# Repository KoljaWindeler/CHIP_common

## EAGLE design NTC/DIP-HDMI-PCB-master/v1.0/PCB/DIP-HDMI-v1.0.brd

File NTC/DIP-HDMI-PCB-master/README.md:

# Source Files
C.H.I.P. HDMI Display DIP is designed using Eagle!

# DIP-HDMI-PCB

HDMI DIP = v1.0

#License
<br />This work is licensed under a <a rel="license" href="http://creativecommons.org/licenses/by-sa/3.0/us/">Creative Commons Attribution-ShareAlike 3.0 United States License</a>.

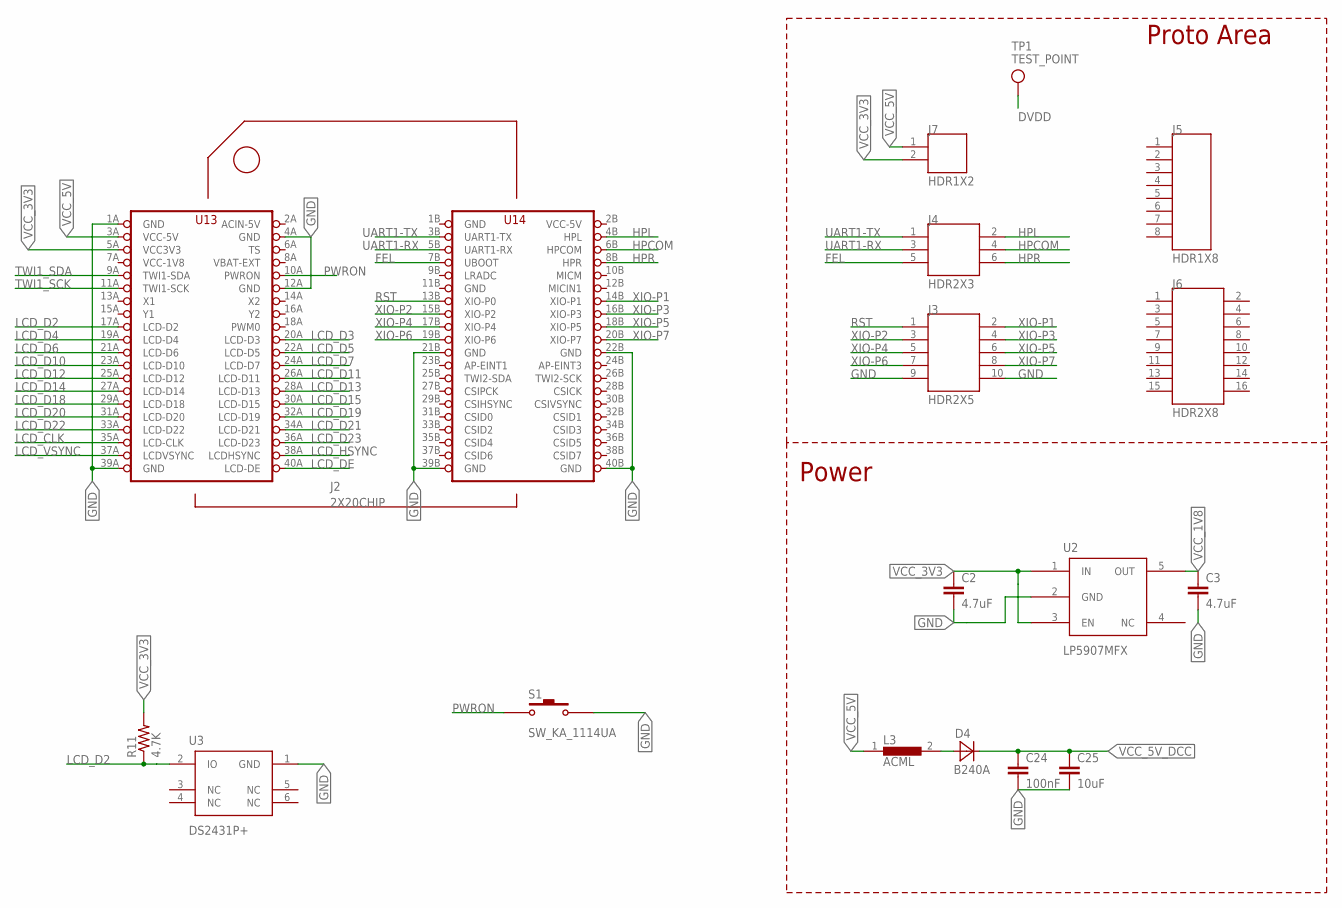
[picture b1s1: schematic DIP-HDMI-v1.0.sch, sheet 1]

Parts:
C2, C3: 4.7uF; 1608_0603
C24: 100nF; 1608_0603
C25: 10uF; 1608_0603
D4: B240A; SMA
J2: 2X20CHIP; HDR2X2X20H
J3: HDR2X5
J4: HDR2X3
J5: HDR1X8
J6: HDR2X8
J7: HDR1X2
L3: ACML; 0603
R11: 4.7K; J1-0603
S1: SW_KA_1114UA
TP1: TEST_POINT; TP-1MMX1MM
U2: LP5907MFX; SOT23-5
U3: DS2431P+; DS2431P+T&R

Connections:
DVDD: TP1.0; also elsewhere on the board
FEL: J2.7B (UBOOT), J4.5
GND: C2.2, C3.2, C24.2, C25.2, J2.1A (GND), J2.1B (GND), J2.4A (GND), J2.11B (GND), J2.12A (GND), J2.21B (GND), J2.22B (GND), J2.39A (GND), J2.39B (GND), J2.40B (GND), J3.9, J3.10, S1.3 (2), S1.4 (2), U2.2 (GND), U3.1 (GND); also elsewhere on the board
HPCOM: J2.6B (HPCOM), J4.4
HPL: J2.4B (HPL), J4.2
HPR: J2.8B (HPR), J4.6
LCD_CLK: J2.35A (LCD-CLK); also elsewhere on the board
LCD_D2: J2.17A (LCD-D2), R11.1, U3.2 (IO)
LCD_D3: J2.20A (LCD-D3); also elsewhere on the board
LCD_D4: J2.19A (LCD-D4); also elsewhere on the board
LCD_D5: J2.22A (LCD-D5); also elsewhere on the board
LCD_D6: J2.21A (LCD-D6); also elsewhere on the board
LCD_D7: J2.24A (LCD-D7); also elsewhere on the board
LCD_D10: J2.23A (LCD-D10); also elsewhere on the board
LCD_D11: J2.26A (LCD-D11); also elsewhere on the board
LCD_D12: J2.25A (LCD-D12); also elsewhere on the board
LCD_D13: J2.28A (LCD-D13); also elsewhere on the board
LCD_D14: J2.27A (LCD-D14); also elsewhere on the board
LCD_D15: J2.30A (LCD-D15); also elsewhere on the board
LCD_D18: J2.29A (LCD-D18); also elsewhere on the board
LCD_D19: J2.32A (LCD-D19); also elsewhere on the board
LCD_D20: J2.31A (LCD-D20); also elsewhere on the board
LCD_D21: J2.34A (LCD-D21); also elsewhere on the board
LCD_D22: J2.33A (LCD-D22); also elsewhere on the board
LCD_D23: J2.36A (LCD-D23); also elsewhere on the board
LCD_DE: J2.40A (LCD-DE); also elsewhere on the board
LCD_HSYNC: J2.38A (LCDHSYNC); also elsewhere on the board
LCD_VSYNC: J2.37A (LCDVSYNC); also elsewhere on the board
unnamed: D4.1 (A), L3.2
PWRON: J2.10A (PWRON), S1.1, S1.2 (1)
RST: J2.13B (XIO-P0), J3.1; also elsewhere on the board
TWI1_SCK: J2.11A (TWI1-SCK); also elsewhere on the board
TWI1_SDA: J2.9A (TWI1-SDA); also elsewhere on the board
UART1-RX: J2.5B (UART1-RX), J4.3
UART1-TX: J2.3B (UART1-TX), J4.1
VCC-1V8: J2.7A (VCC-1V8)
VCC-5V: J2.2B (VCC-5V)
VCC_1V8: C3.1, U2.5 (OUT); also elsewhere on the board
VCC_3V3: C2.1, J2.5A (VCC3V3), J7.2, R11.2, U2.1 (IN), U2.3 (EN); also elsewhere on the board
VCC_5V: J2.3A (VCC-5V), J7.1, L3.1
VCC_5V_DCC: C24.1, C25.1, D4.2 (C); also elsewhere on the board
XIO-P1: J2.14B (XIO-P1), J3.2
XIO-P2: J2.15B (XIO-P2), J3.3
XIO-P3: J2.16B (XIO-P3), J3.4
XIO-P4: J2.17B (XIO-P4), J3.5
XIO-P5: J2.18B (XIO-P5), J3.6
XIO-P6: J2.19B (XIO-P6), J3.7
XIO-P7: J2.20B (XIO-P7), J3.8

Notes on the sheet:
Proto Area
Power

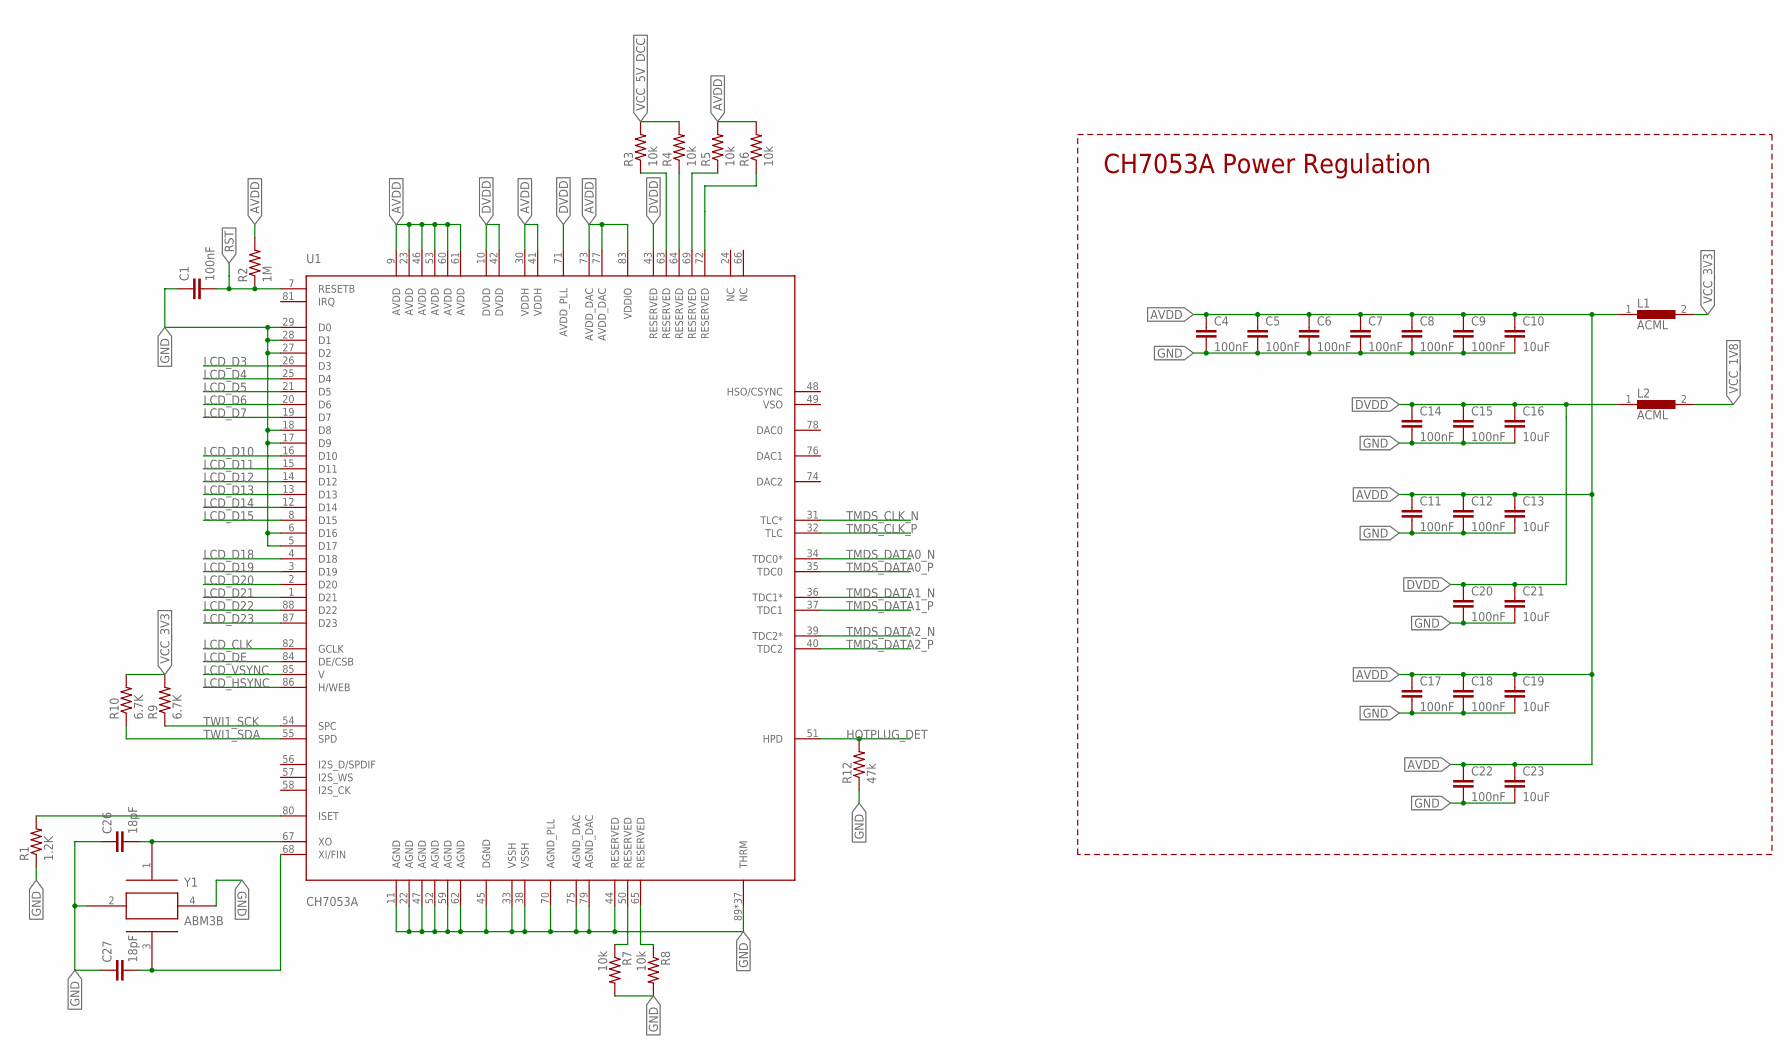
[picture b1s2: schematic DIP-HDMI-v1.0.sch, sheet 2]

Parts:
C1, C4, C5, C6, C7, C8, C9, C11, C12, C14, C15, C17, C18, C20, C22: 100nF; 1608_0603
C10, C13, C16, C19, C21, C23: 10uF; 1608_0603
C26, C27: 18pF; 1608_0603
L1, L2: ACML; 0603
R1: 1.2K; J1-0603
R2: 1M; J1-0603
R3, R4, R5, R6, R7, R8: 10k; J1-0603
R9, R10: 6.7K; J1-0603
R12: 47k; J1-0603
U1: CH7053A; QFN40P1000X1000X90_HS-89M
Y1: ABM3B

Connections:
AVDD: C4.1, C5.1, C6.1, C7.1, C8.1, C9.1, C10.1, C11.1, C12.1, C13.1, C17.1, C18.1, C19.1, C22.1, C23.1, L1.1, R2.2, R5.2, R6.2, U1.9 (AVDD), U1.23 (AVDD), U1.30 (VDDH), U1.41 (VDDH), U1.46 (AVDD), U1.53 (AVDD), U1.60 (AVDD), U1.61 (AVDD), U1.73 (AVDD_DAC), U1.77 (AVDD_DAC), U1.83 (VDDIO)
DVDD: C14.1, C15.1, C16.1, C20.1, C21.1, L2.1, U1.10 (DVDD), U1.42 (DVDD), U1.43 (RESERVED), U1.71 (AVDD_PLL); also elsewhere on the board
GND: C1.1, C4.2, C5.2, C6.2, C7.2, C8.2, C9.2, C10.2, C11.2, C12.2, C13.2, C14.2, C15.2, C16.2, C17.2, C18.2, C19.2, C20.2, C21.2, C22.2, C23.2, C26.1, C27.1, R1.1, R7.2, R8.2, R12.1, U1.5 (D17), U1.6 (D16), U1.11 (AGND), U1.17 (D9), U1.18 (D8), U1.22 (AGND), U1.27 (D2), U1.28 (D1), U1.29 (D0), U1.33 (VSSH), U1.38 (VSSH), U1.44 (RESERVED), U1.45 (DGND), U1.47 (AGND), U1.52 (AGND), U1.59 (AGND), U1.62 (AGND), U1.70 (AGND_PLL), U1.75 (AGND_DAC), U1.79 (AGND_DAC), U1.89 (THRM), U1.P$1 (THRM), U1.P$2 (THRM), U1.P$3 (THRM), U1.P$4 (THRM), U1.P$5 (THRM), U1.P$6 (THRM), U1.P$7 (THRM), U1.P$8 (THRM), U1.P$9 (THRM), U1.P$10 (THRM), U1.P$11 (THRM), U1.P$12 (THRM), U1.P$13 (THRM), U1.P$14 (THRM), U1.P$15 (THRM), U1.P$16 (THRM), U1.P$17 (THRM), U1.P$18 (THRM), U1.P$19 (THRM), U1.P$20 (THRM), U1.P$21 (THRM), U1.P$22 (THRM), U1.P$23 (THRM), U1.P$24 (THRM), U1.P$25 (THRM), U1.P$26 (THRM), U1.P$27 (THRM), U1.P$28 (THRM), U1.P$29 (THRM), U1.P$30 (THRM), U1.P$31 (THRM), U1.P$32 (THRM), U1.P$33 (THRM), U1.P$34 (THRM), U1.P$35 (THRM), U1.P$36 (THRM), Y1.2, Y1.4; also elsewhere on the board
HOTPLUG_DET: R12.2, U1.51 (HPD); also elsewhere on the board
LCD_CLK: U1.82 (GCLK); also elsewhere on the board
LCD_D3: U1.26 (D3); also elsewhere on the board
LCD_D4: U1.25 (D4); also elsewhere on the board
LCD_D5: U1.21 (D5); also elsewhere on the board
LCD_D6: U1.20 (D6); also elsewhere on the board
LCD_D7: U1.19 (D7); also elsewhere on the board
LCD_D10: U1.16 (D10); also elsewhere on the board
LCD_D11: U1.15 (D11); also elsewhere on the board
LCD_D12: U1.14 (D12); also elsewhere on the board
LCD_D13: U1.13 (D13); also elsewhere on the board
LCD_D14: U1.12 (D14); also elsewhere on the board
LCD_D15: U1.8 (D15); also elsewhere on the board
LCD_D18: U1.4 (D18); also elsewhere on the board
LCD_D19: U1.3 (D19); also elsewhere on the board
LCD_D20: U1.2 (D20); also elsewhere on the board
LCD_D21: U1.1 (D21); also elsewhere on the board
LCD_D22: U1.88 (D22); also elsewhere on the board
LCD_D23: U1.87 (D23); also elsewhere on the board
LCD_DE: U1.84 (DE/CSB); also elsewhere on the board
LCD_HSYNC: U1.86 (H/WEB); also elsewhere on the board
LCD_VSYNC: U1.85 (V); also elsewhere on the board
unnamed: C26.2, U1.67 (XO), Y1.1
unnamed: C27.2, U1.68 (XI/FIN), Y1.3
unnamed: R1.2, U1.80 (ISET)
unnamed: R7.1, U1.50 (RESERVED)
unnamed: R8.1, U1.65 (RESERVED)
unnamed: R5.1, U1.69 (RESERVED)
unnamed: R3.1, U1.63 (RESERVED)
unnamed: R4.1, U1.64 (RESERVED)
unnamed: R6.1, U1.72 (RESERVED)
RST: C1.2, R2.1, U1.7 (RESETB); also elsewhere on the board
TMDS_CLK_N: U1.31 (TLC*); also elsewhere on the board
TMDS_CLK_P: U1.32 (TLC); also elsewhere on the board
TMDS_DATA0_N: U1.34 (TDC0*); also elsewhere on the board
TMDS_DATA0_P: U1.35 (TDC0); also elsewhere on the board
TMDS_DATA1_N: U1.36 (TDC1*); also elsewhere on the board
TMDS_DATA1_P: U1.37 (TDC1); also elsewhere on the board
TMDS_DATA2_N: U1.39 (TDC2*); also elsewhere on the board
TMDS_DATA2_P: U1.40 (TDC2); also elsewhere on the board
TWI1_SCK: R9.1, U1.54 (SPC); also elsewhere on the board
TWI1_SDA: R10.1, U1.55 (SPD); also elsewhere on the board
VCC_1V8: L2.2; also elsewhere on the board
VCC_3V3: L1.2, R9.2, R10.2; also elsewhere on the board
VCC_5V_DCC: R3.2, R4.2; also elsewhere on the board

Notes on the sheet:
CH7053A Power Regulation

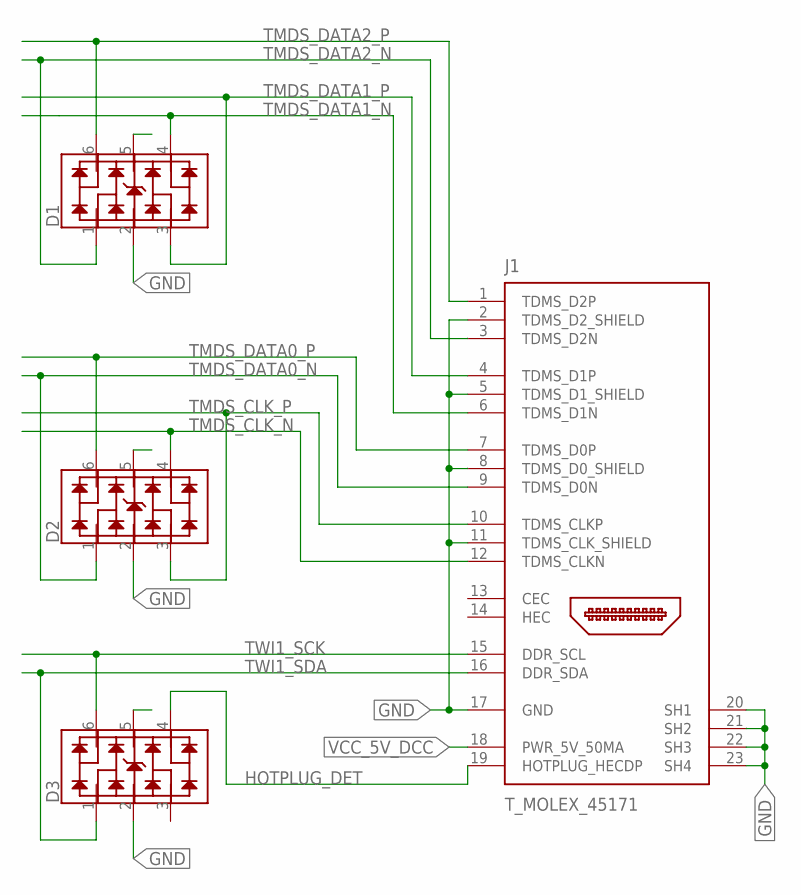
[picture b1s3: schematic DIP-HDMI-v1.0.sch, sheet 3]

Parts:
D1, D2, D3: D-SEMTECH-RCLAMP0504S; T_SOT95P285X90-6N
J1: T_MOLEX_45171

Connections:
GND: D1.2, D2.2, D3.2, J1.2 (TDMS_D2_SHIELD), J1.5 (TDMS_D1_SHIELD), J1.8 (TDMS_D0_SHIELD), J1.11 (TDMS_CLK_SHIELD), J1.17 (GND), J1.20 (SH1), J1.21 (SH2), J1.22 (SH3), J1.23 (SH4); also elsewhere on the board
HOTPLUG_DET: D3.4, J1.19 (HOTPLUG_HECDP); also elsewhere on the board
TMDS_CLK_N: D2.4, J1.12 (TDMS_CLKN); also elsewhere on the board
TMDS_CLK_P: D2.3, J1.10 (TDMS_CLKP); also elsewhere on the board
TMDS_DATA0_N: D2.1, J1.9 (TDMS_D0N); also elsewhere on the board
TMDS_DATA0_P: D2.6, J1.7 (TDMS_D0P); also elsewhere on the board
TMDS_DATA1_N: D1.4, J1.6 (TDMS_D1N); also elsewhere on the board
TMDS_DATA1_P: D1.3, J1.4 (TDMS_D1P); also elsewhere on the board
TMDS_DATA2_N: D1.1, J1.3 (TDMS_D2N); also elsewhere on the board
TMDS_DATA2_P: D1.6, J1.1 (TDMS_D2P); also elsewhere on the board
TWI1_SCK: D3.6, J1.15 (DDR_SCL); also elsewhere on the board
TWI1_SDA: D3.1, J1.16 (DDR_SDA); also elsewhere on the board
VCC_5V_DCC: J1.18 (PWR_5V_50MA); also elsewhere on the board

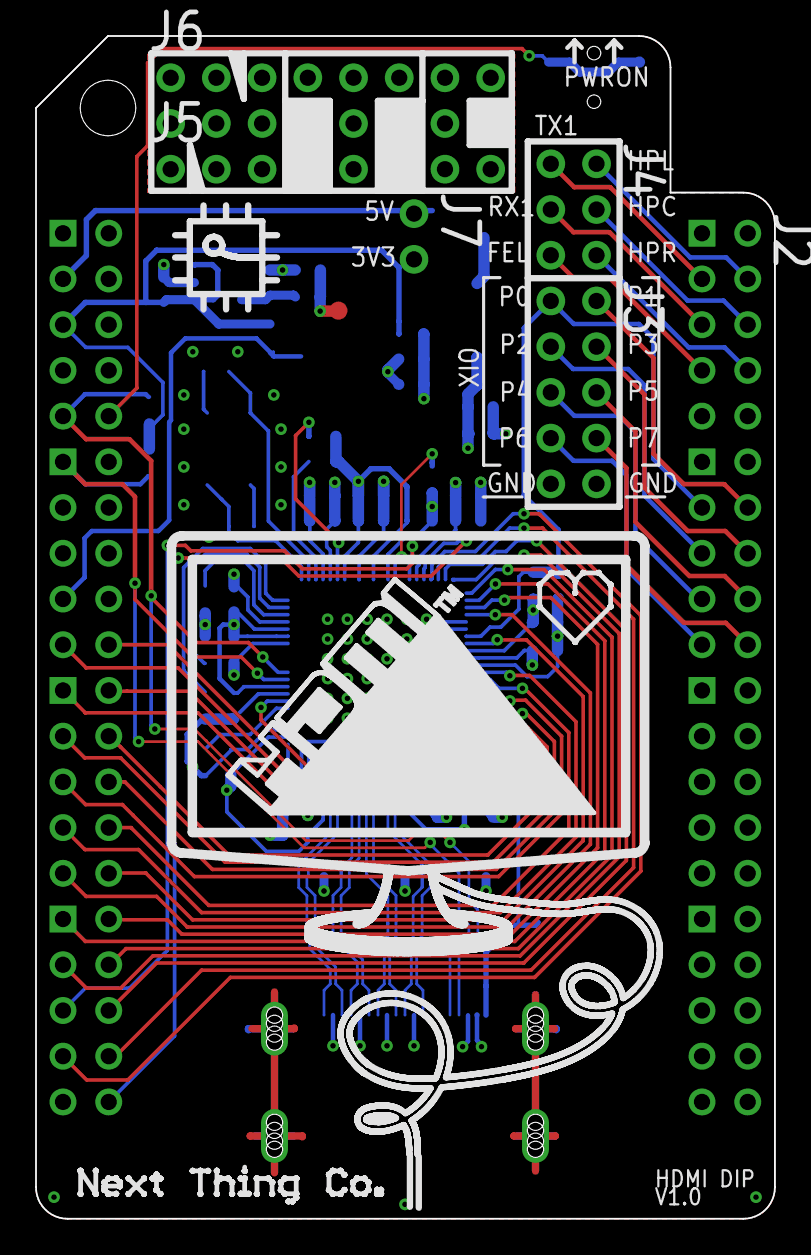
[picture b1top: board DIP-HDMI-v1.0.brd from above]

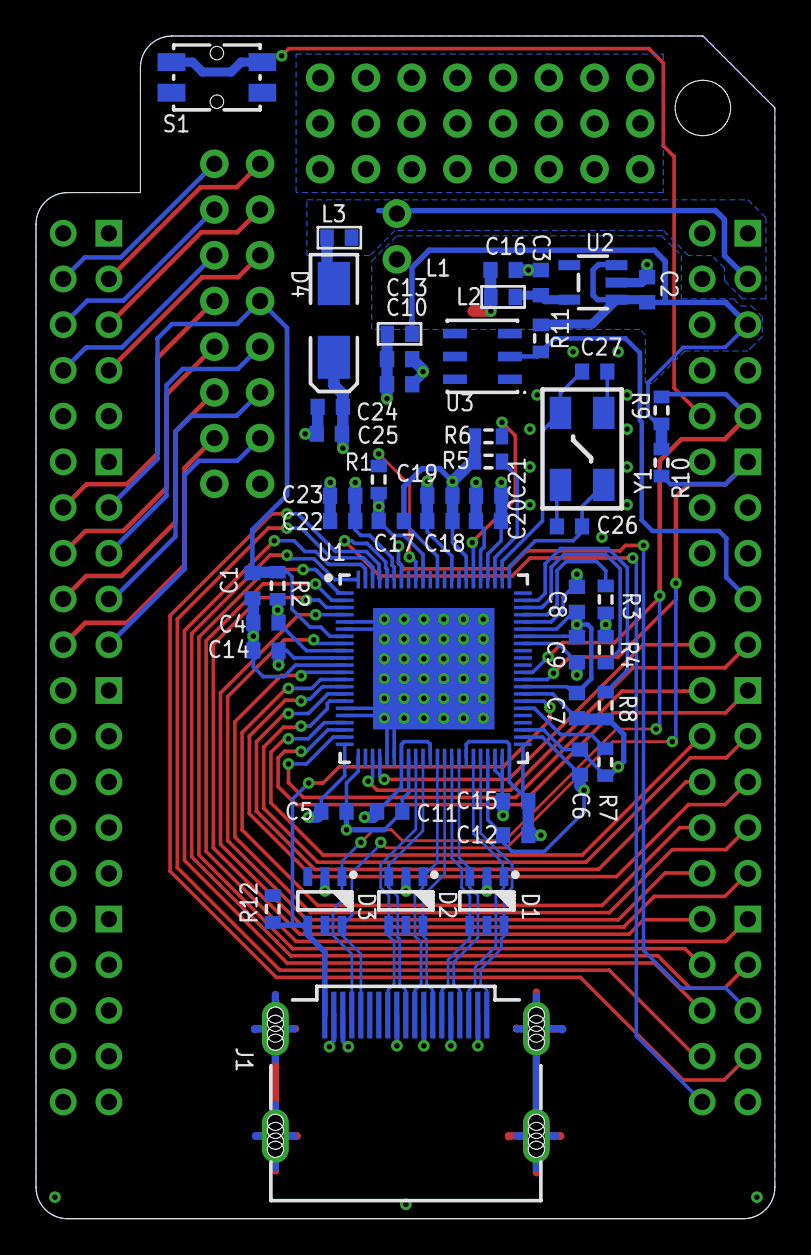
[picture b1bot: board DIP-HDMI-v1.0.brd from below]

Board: 4 copper layers, 41.0 x 65.7 mm, 60 parts (52 on the bottom side), 65 nets.

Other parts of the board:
U$2: MOUNTINGHOLE

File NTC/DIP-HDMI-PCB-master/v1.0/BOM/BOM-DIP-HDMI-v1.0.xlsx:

| Company = Next Thing Co
 | Design Title =HDMI Adapter
 | Doc Name: BOM-DIP-HDMI-v1.0.xlsx
 | Matching PCB: DIP-HDMI-v1.0.brd
 | Schematics REV: 1.0
 | Qty | Parts | VALUE | Item number | TOLERANCE | DESCRIPTION | FOOTPRINT | MFG | MFG_PN | PART_TYPE
 | 16 | C1, C4, C5, C6, C7, C8, C9, C11, C12, C14, C15, C17, C18, C20, C22, C24 | 100nF | 100364 | 0.1 | CAP CER SMD 100nF 16V X5R 10% 0603 | 0603 | SAMSUNG | CL10B104KO8NNNL | CAP
 | 2 | C2, C3 | 4.7uF | 100365 | 0.1 | CAP CER SMD 4.7uF 10V X5R 10% 0603 | 0603 | SAMSUNG | CL10A475KP8NNNL | CAP
 | 7 | C10, C13, C16, C19, C21, C23, C25 | 10uF | 100366 | 0.1 | CAP CER SMD 10uF 10V X5R 10% 0603 | 0603 | SAMSUNG | CL10A106KP8NNND | CAP
 | 2 | C26, C27 | 18pF | 100367 | 0.01 | CAP CER SMD 18pF 50V NP0 1% 0603 | 0603 | SAMSUNG | CL10C180JB8NNND | CAP
 | 1 | J1 | HDMI Con | 100402 |  | Connector Receptacle HDMI 19 Position Surface Mount, Right Angle, Horizontal |  | Zhixingda | 71-050-190111-1 | CON
 | 2 | J2A, J2B | CON2X20 | 100401 |  | 2x Con male through hole 40 pos, 2 rows, 2.54MM | 2XHDR_40POS_PTH_254MM | TE Connectivity | 2 x 1-102567-2 | CON
 | 1 | R1 | 1.2k | 100368 | 0.01 | RES SMD 1.2K Ohm 1/16W 1% 0603 | 0603 | YAGEO | RC0603FR-071K2L | RES
 | 1 | R2 | 1M | 100369 | 0.05 | RES SMD 1M Ohm 1/16W 5% 0603 | 0603 | YAGEO | RC0603JR-071ML | RES
 | 6 | R3, R4, R5, R6, R7, R8 | 10k | 100370 | 0.05 | RES SMD 10K Ohm 1/16W 5% 0603 | 0603 | YAGEO | RC0603JR-0710KL | RES
 | 2 | R9, R10 | 6.8k | 100406 | 0.05 | RES SMD 6.8K Ohm 1/16W 5% 0603 | 0603 | YAGEO | RC0603JR-076K8L | RES
 | 1 | R11 | 4.7k | 100380 | 0.05 | RES SMD 4.7K Ohm 1/16W 5% 0603 | 0603 | YAGEO | RC0603JR-074K7L | RES
 | 1 | R12 | 47k | 100381 | 0.05 | RES SMD 47K Ohm 1/16W 5% 0603 | 0603 | YAGEO | RC0603JR-0747KL | RES
 | 1 | D4 | B240A | 100198 |  | DIODE SMD General Purpose 400V 1A 1.4W RoHS DO-214AC | SMA | DIODES INC | B240A-13-F | DIODE
 | 3 | D1, D2, D3 | SESRV05-4 | 100415 |  | LOW CAP TVS ARRAY | SOT-23 6 | SEMIWILL | SESRV05-4 | TVS DIODE
 | 3 | L1, L2, L3 | ACML0603 | 100417 |  | SMD Ferrite 0603, 31 Ohm @ 100MHz | 0603 | Abracon | ACML-0603-310-T | FB
 | 1 | U1 | CH7035B | 100404 |  | IC, LDC to HDTV/VGA/DVI, QFN88 | QFN88 | Chrontel | CH7035B | IC
 | 1 | U2 | BL9198-18 | 100416 |  | LDO SMD, 1.8V, 250mA SOT-23 | SOT-23 5 | Shanghai Belling | BL9198-18 | IC
 | 1 | U3 | DS2431 | 100312 |  | IC, EEPROM, 1KBIT, TSOC 6 | TSOC 6 | Maxim Integrated | DS2431P+T&R | IC
 | 1 | Y1 | ABM3B | 100418 |  | CRYSTAL SMD 5X3.2 27Mhz 20ppm 18pF | 5X3.2mm | Abracon | ABM3B-27.000MHZ-B2-T | XTAL
 | 1 |  | PCB | 100422 |  | 4 Layer, Matte Black Mask, Pink Silk, HASL, 1 Oz |  |  | v1.0 | PCB
 | 1 |  |  |  |  | ESD BAG |  |  |  | PACKAGING
 | 1 |  |  |  |  | ESD Foam, Back Side |  |  |  | PACKAGING
 | 1 |  |  |  |  | ESD Foam, Front Side |  |  |  | PACKAGING
 | 1 | S1 | Switch | 100421 |  | Tact Switch Right Angle | 2.7X6.6mm | HRD | KA-1114UN | Switch

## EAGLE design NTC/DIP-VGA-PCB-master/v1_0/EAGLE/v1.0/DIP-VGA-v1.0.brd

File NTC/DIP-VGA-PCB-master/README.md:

# Source Files
VGA DIP is designed using Eagle CAD!

# DIP-VGA-PCB
VGA DIP = v1.0

#License
<br />This work is licensed under a <a rel="license" href="http://creativecommons.org/licenses/by-sa/3.0/us/">Creative Commons Attribution-ShareAlike 3.0 United States License</a>.

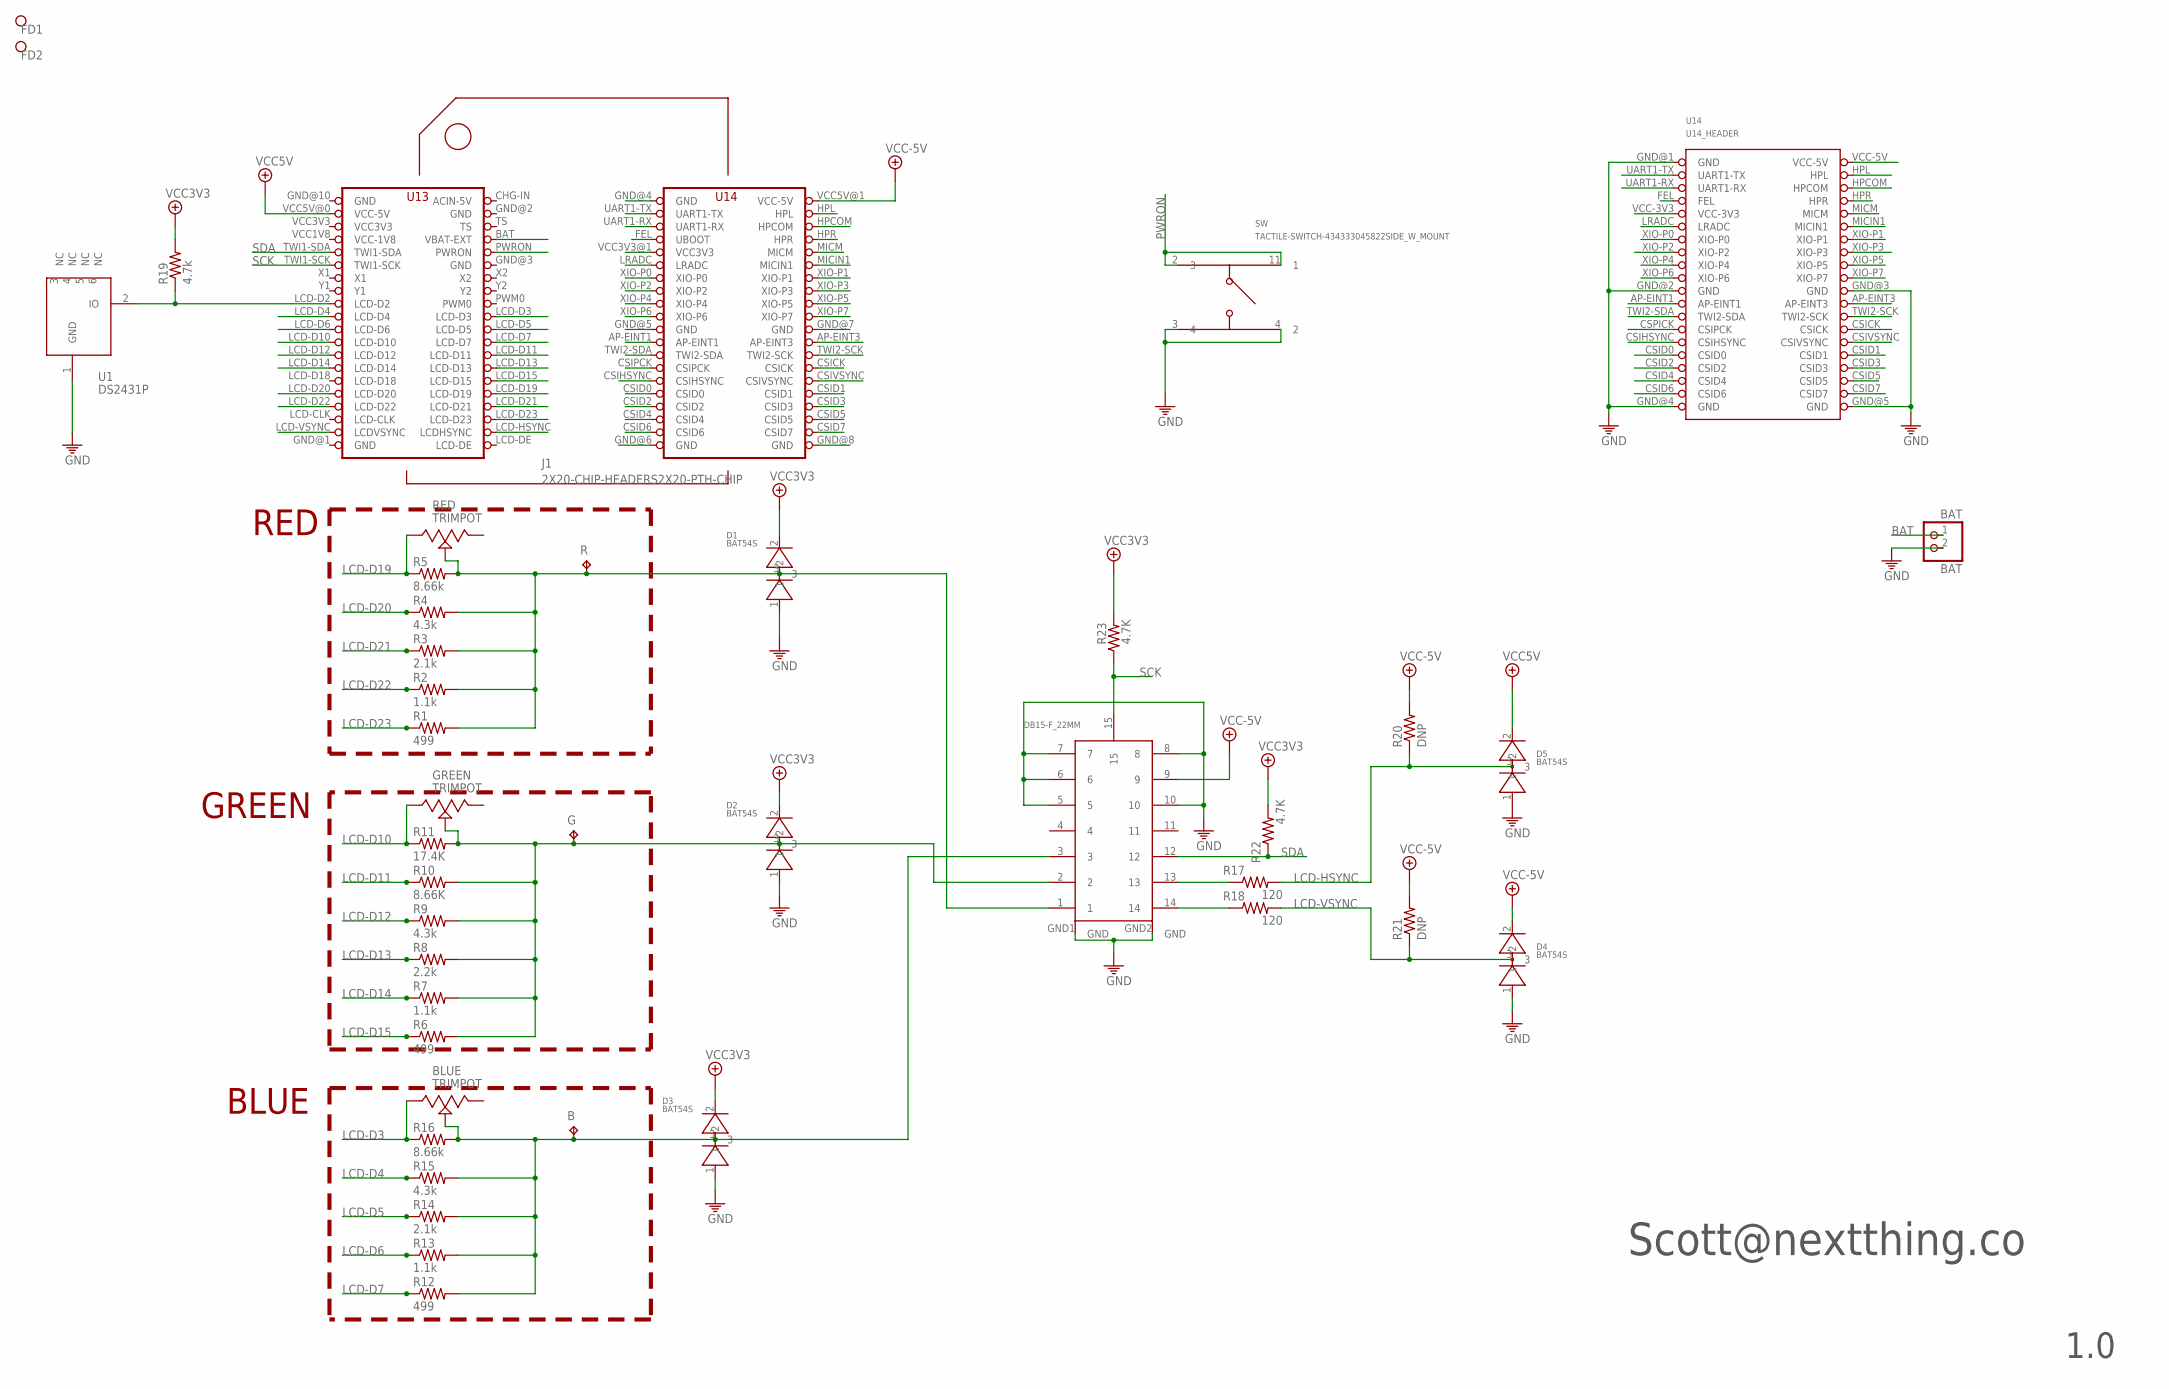
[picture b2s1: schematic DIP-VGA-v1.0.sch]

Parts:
B: TPPAD1-17; P1-17
BAT: BAT; JST-PH-2-THM-RA
BLUE: TRIMPOT
D1, D2, D3, D4, D5: BAT54S; SOT23-BEC
FD1, FD2: FIDUCIAL; FIDUCIAL_1MM
G: TPPAD1-17; P1-17
GREEN: TRIMPOT
J1: 2X20-CHIP-HEADERS2X20-PTH-CHIP; 2X20CHIP-TH
R: TPPAD1-17; P1-17
R1, R6, R12: 499; R0603_5MIL_DWS
R2, R7, R13: 1.1k; R0603_5MIL_DWS
R3, R14: 2.1k; R0603_5MIL_DWS
R4, R9, R15: 4.3k; R0603_5MIL_DWS
R5, R16: 8.66k; R0603_5MIL_DWS
R8: 2.2k; R0603_5MIL_DWS
R10: 8.66K; R0603_5MIL_DWS
R11: 17.4K; R0603_5MIL_DWS
R17, R18: 120; R0603_5MIL_DWS
R19: 4.7k; R0603_5MIL_DWS
R20, R21: DNP; R0603_5MIL_DWS
R22, R23: 4.7K; R0603_5MIL_DWS
RED: TRIMPOT
SW: TACTILE-SWITCH-434333045822SIDE_W_MOUNT; TACTILE-SWITCH-K2-1114UA-AW
TRANS(>^_^)>: DB15-F_22MM
U1: DS2431P; TSOC6
U14: U14_HEADER; U14HEADER

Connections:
1: J1.CSIVSYNC, U14.CSIVSYNC
AP-EINT1: J1.AP-EINT1, U14.AP-EINT1
AP-EINT3: J1.AP-EINT3, U14.AP-EINT3
BAT: BAT.1 (2), J1.BAT (VBAT-EXT)
CSICK: J1.CSICK, U14.CSICK
CSID0: J1.CSID0, U14.CSID0
CSID1: J1.CSID1, U14.CSID1
CSID2: J1.CSID2, U14.CSID2
CSID3: J1.CSID3, U14.CSID3
CSID4: J1.CSID4, U14.CSID4
CSID5: J1.CSID5, U14.CSID5
CSID6: J1.CSID6, U14.CSID6
CSID7: J1.CSID7, U14.CSID7
CSIHSYNC: J1.CSIHSYNC, U14.CSIHSYNC
CSPICK: J1.CSIPCK, U14.CSPICK (CSIPCK)
FEL: J1.FEL (UBOOT), U14.FEL
GND: BAT.2 (1), D1.1, D2.1, D3.1, D4.1, D5.1, J1.GND@1 (GND), J1.GND@2 (GND), J1.GND@3 (GND), J1.GND@4 (GND), J1.GND@5 (GND), J1.GND@6 (GND), J1.GND@7 (GND), J1.GND@8 (GND), J1.GND@10 (GND), SW.3 (4), SW.4 (2), TRANS(>^_^)>.5, TRANS(>^_^)>.6, TRANS(>^_^)>.7, TRANS(>^_^)>.8, TRANS(>^_^)>.10, TRANS(>^_^)>.GND1 (GND), TRANS(>^_^)>.GND2 (GND), U1.1 (GND), U14.GND@1 (GND), U14.GND@2 (GND), U14.GND@3 (GND), U14.GND@4 (GND), U14.GND@5 (GND)
HPCOM: J1.HPCOM, U14.HPCOM
HPL: J1.HPL, U14.HPL
HPR: J1.HPR, U14.HPR
LCD-D3: BLUE.3, J1.LCD-D3, R16.1
LCD-D4: J1.LCD-D4, R15.1
LCD-D5: J1.LCD-D5, R14.1
LCD-D6: J1.LCD-D6, R13.1
LCD-D7: J1.LCD-D7, R12.1
LCD-D10: GREEN.3, J1.LCD-D10, R11.1
LCD-D11: J1.LCD-D11, R10.1
LCD-D12: J1.LCD-D12, R9.1
LCD-D13: J1.LCD-D13, R8.1
LCD-D14: J1.LCD-D14, R7.1
LCD-D15: J1.LCD-D15, R6.1
LCD-D19: J1.LCD-D19, R5.1, RED.3
LCD-D20: J1.LCD-D20, R4.1
LCD-D21: J1.LCD-D21, R3.1
LCD-D22: J1.LCD-D22, R2.1
LCD-D23: J1.LCD-D23, R1.1
LCD-HSYNC: D5.3, J1.LCD-HSYNC (LCDHSYNC), R17.2, R20.1
LCD-VSYNC: D4.3, J1.LCD-VSYNC (LCDVSYNC), R18.2, R21.1
LRADC: J1.LRADC, U14.LRADC
MICIN1: J1.MICIN1, U14.MICIN1
MICM: J1.MICM, U14.MICM
unnamed: R17.1, TRANS(>^_^)>.13
unnamed: R18.1, TRANS(>^_^)>.14
unnamed: J1.LCD-D2, R19.1, U1.2 (IO)
unnamed: D2.3, G.TP, GREEN.2, R6.2, R7.2, R8.2, R9.2, R10.2, R11.2, TRANS(>^_^)>.2
unnamed: D1.3, R.TP, R1.2, R2.2, R3.2, R4.2, R5.2, RED.2, TRANS(>^_^)>.1
unnamed: B.TP, BLUE.2, D3.3, R12.2, R13.2, R14.2, R15.2, R16.2, TRANS(>^_^)>.3
PWRON: J1.PWRON, SW.2 (3), SW.11 (1)
SCK: J1.TWI1-SCK, R23.1, TRANS(>^_^)>.15
SDA: J1.TWI1-SDA, R22.1, TRANS(>^_^)>.12
TWI2-SCK: J1.TWI2-SCK, U14.TWI2-SCK
TWI2-SDA: J1.TWI2-SDA, U14.TWI2-SDA
UART1-RX: J1.UART1-RX, U14.UART1-RX
UART1-TX: J1.UART1-TX, U14.UART1-TX
VCC3V3: D1.2, D2.2, D3.2, J1.VCC3V3, J1.VCC3V3@1 (VCC3V3), R19.2, R22.2, R23.2, U14.VCC-3V3
VCC5V: D4.2, D5.2, J1.VCC5V@0 (VCC-5V), J1.VCC5V@1 (VCC-5V), R20.2, R21.2, TRANS(>^_^)>.9, U14.VCC-5V
VCC-1V8: J1.VCC1V8 (VCC-1V8)
XIO-P0: J1.XIO-P0, U14.XIO-P0
XIO-P1: J1.XIO-P1, U14.XIO-P1
XIO-P2: J1.XIO-P2, U14.XIO-P2
XIO-P3: J1.XIO-P3, U14.XIO-P3
XIO-P4: J1.XIO-P4, U14.XIO-P4
XIO-P5: J1.XIO-P5, U14.XIO-P5
XIO-P6: J1.XIO-P6, U14.XIO-P6
XIO-P7: J1.XIO-P7, U14.XIO-P7

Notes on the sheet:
RED
GREEN
BLUE
Scott@nextthing.co
1.0

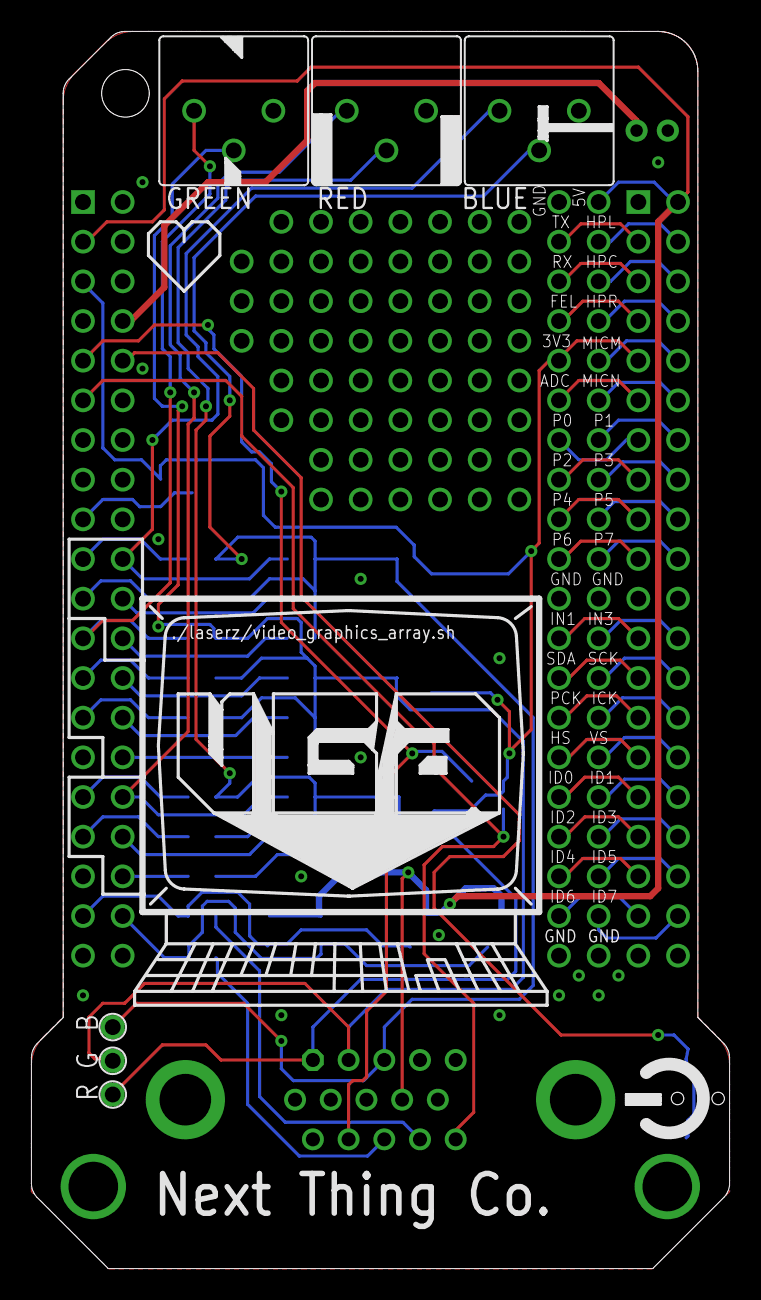
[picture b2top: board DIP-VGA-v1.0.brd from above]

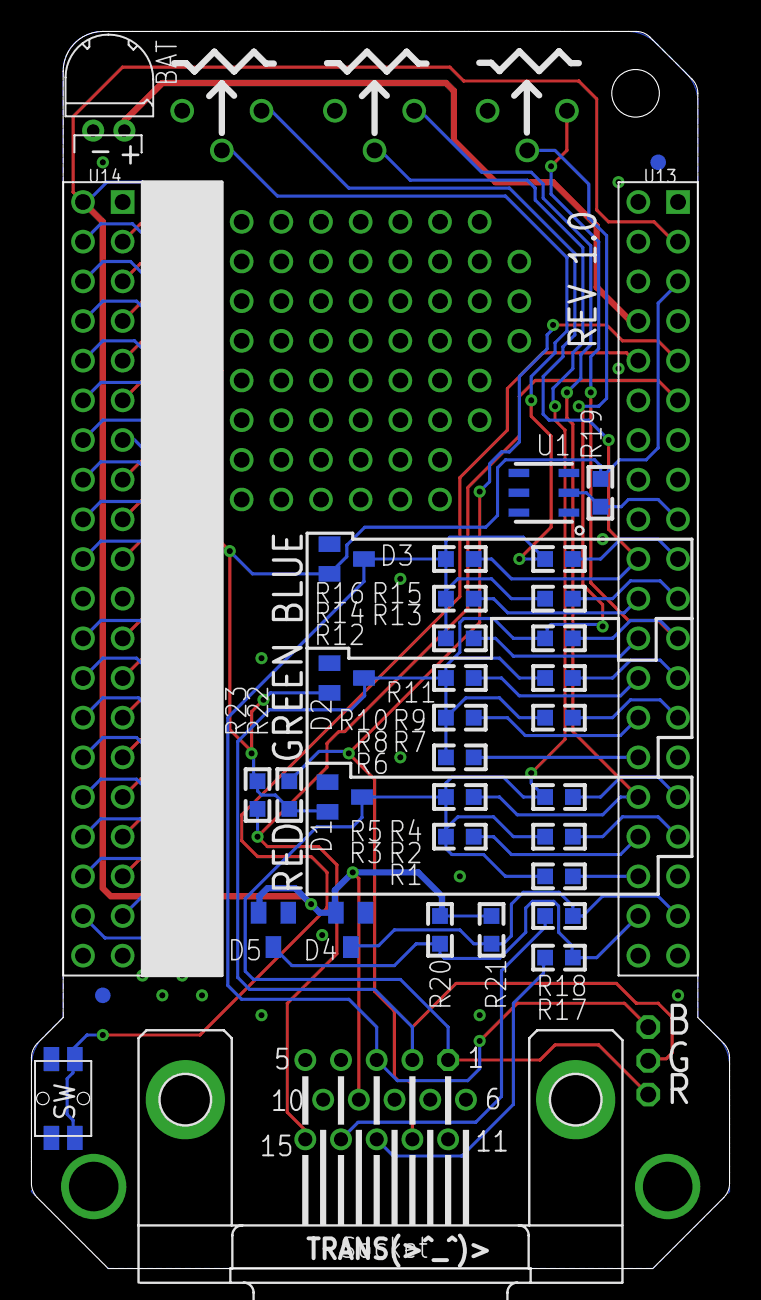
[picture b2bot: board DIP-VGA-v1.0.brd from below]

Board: 4 copper layers, 44.7 x 79.2 mm, 42 parts (34 on the bottom side), 64 nets.

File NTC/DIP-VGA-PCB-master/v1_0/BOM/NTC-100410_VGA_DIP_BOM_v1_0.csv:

quantity,reference_designator,item_number,item_name,revision,item_category,Package,Power Rating,Resistance,Tolerance
 , ,100410,VGA_DIP PCB,1,Custom PCB assembly, , , , 
5,"D1, D2, D3, D4, D5",100129,SMD DIODE BAT54S SOT-23,1,Diode, , , , 
1,U1,100312,DS2431P+T&R,1,IC,6-TSOC, , , 
2,"R3, R14",100385,RES SMD 2.1K OHM 1% 1/10W 0603,1,Resistor,603,1/10W,2.1K½,1%
1,R8,100386,RES SMD 2.2K OHM 1% 1/10W 0603,1,Resistor,603,1/10W,2.2K½,1%
3,"R4, R9, R15",100387,RES SMD 4.3K OHM 1% 1/10W 0603,1,Resistor,603,1/10W,4.3K½,1%
3,"R1, R6, R12",100389,RES SMD 499 OHM 0.5% 0.15W 0603,1,Resistor,603,0.15,499½,0.50%
3,"R5, R16, R10",100390,RES SMD 8.66K OHM 1% 1/10W 0603,1,Resistor,603,1/10W,8.66K½,1%
3,"R22, R23, R19",100393,RES SMD 4.7K OHM 1% 1/10W 0603,1,Resistor,603,1/10W,4.7K½,1%
2,"U13, U14",100401,SMT CONN HEADER VERT DUAL 40POS  GOLD,1,Jack, , , , 
1,DB15,100405,"15 Position D-Sub,Female Sockets, SMT VGA Connector",1,Jack, , , , 
3,"R2, R7, R13",100411,1.1K© RESISTOR ±1%,1,Resistor,603,1/10w,1.1K½,1%
2,"R17, R18",100412,120© RESISTOR 0603 ±1%,1,Resistor,603,1/10w,120½,1%
1,R11,100413,17.4K © RESISTOR 0603 ±1%,1,Resistor,603,1/10w,17.4K½,1%
1,SW,100425,TACTILE-SWITCH-K2-1114UA,1,Switch,, , , 
DNP,"R20, R21",100426,DO NOT POPULATE,1,Resistor,603,1/10w,1K½,603

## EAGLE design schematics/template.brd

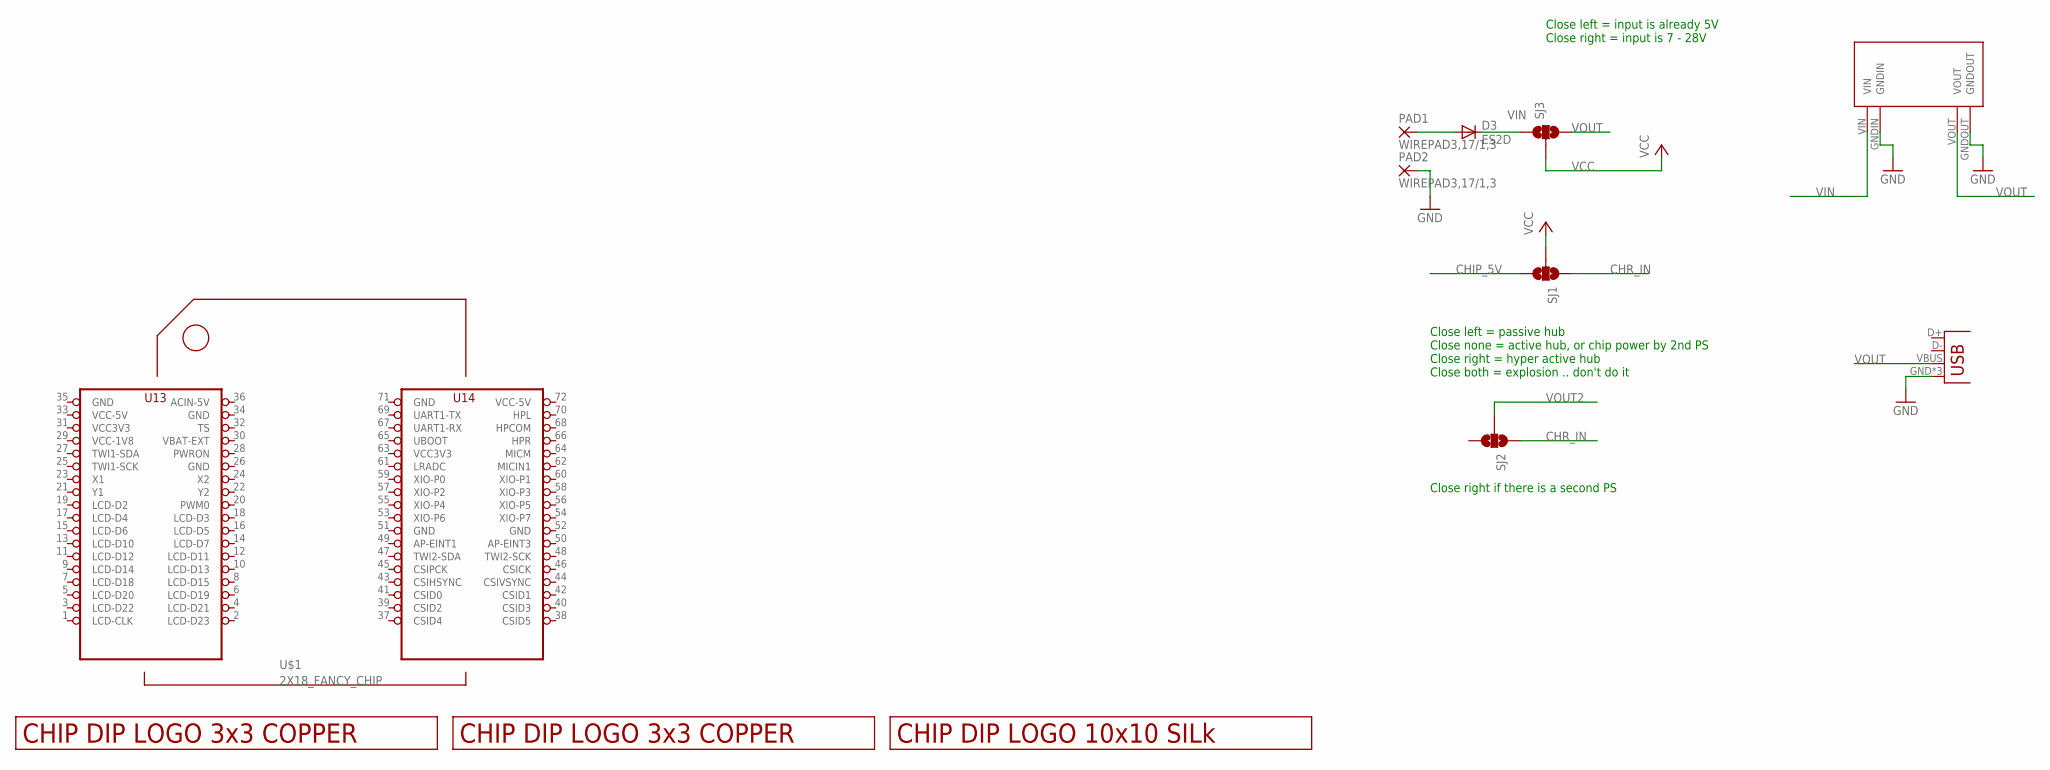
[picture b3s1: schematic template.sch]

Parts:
D3: ES2D; SMB
PAD1, PAD2: WIREPAD3,17/1,3; 3,17/1,3
POWER_USB: USBUSB-MICROB-SMT-DIP; USB-MICROB-SMT-DIP
SJ1, SJ2, SJ3: SOLDERJUMPER_2WAYT; SJ_2
U$1: 2X18_FANCY_CHIP; 2X18_FANCY_EDGE_CHIP_TH
U$4, U$5: LOGO_3X3_COPPER
U$6: LOGO_10X10_SILK
U$9: MP1584EN

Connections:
CHIP_5V: SJ1.3
CHR_IN: SJ1.1, SJ2.1
GND: PAD2.1, POWER_USB.GND, POWER_USB.MT1 (GND), POWER_USB.MT2 (GND), U$1.26 (GND), U$1.34 (GND), U$1.35 (GND), U$1.51 (GND), U$1.52 (GND), U$1.71 (GND), U$9.GNDIN, U$9.GNDOUT
unnamed: D3.A, PAD1.1
VCC: SJ1.2, SJ3.2
VCC3V3: U$1.31 (VCC3V3), U$1.63 (VCC3V3)
VCC-1V8: U$1.29 (VCC-1V8)
VCC-5V: U$1.33 (VCC-5V), U$1.72 (VCC-5V)
VIN: D3.C, SJ3.1, U$9.VIN
VOUT: POWER_USB.VBUS, SJ3.3, U$9.VOUT
VOUT2: SJ2.2

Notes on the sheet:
Close left = passive hub Close none = active hub, or chip power by 2nd PS Close right = hyper active hub Close both = explosion .. don't do it
Close left = input is already 5V Close right = input is 7 - 28V
Close right if there is a second PS

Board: 2 copper layers, 12 parts (0 on the bottom side), 8 nets, no tracks yet.

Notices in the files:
parts and their libraries:
SparkFun-Retired: Licensing:Creative Commons ShareAlike 4.0 International - https://creativecommons.org/licenses/by-sa/4.0
